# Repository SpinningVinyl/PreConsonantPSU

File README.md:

# PreConsonant PSU

### Basic Information

This is a 24V PSU I designed for use with the [PreConsonant phono preamplifier](https://github.com/SpinningVinyl/PreConsonant2021). It is basically a discrete feedback regulator with an error amplifier consisting of a single transistor (Q2 on the circuit diagram). It is designed to be used with a 24V transformer because I wanted to use an off-the-shelf 24V AC wall wart to power my phono preamplifier build. Since transformers typically have no-load output voltage that can be up to 20% higher than their rated voltage under full load, it was going to be too high for a standard 3-pin voltage regulator IC (e.g. LM7824).

### Technical specifications

 - Input voltage: between 21 and 30V AC (with the specified components)
 - Output voltage: approx. 24V DC
 - Load regulation: less than 1% at 100mA output current (component values have been calculated for output currents up to 500mA)
 - Ripple and noise: more than 60dB below the output level
 
### Documentation
The documentation (bill of materials and full circuit diagram) is located in the `docs` folder.

### Status of the project

The project has been built and tested.

### License
See the `LICENSE` file for details.

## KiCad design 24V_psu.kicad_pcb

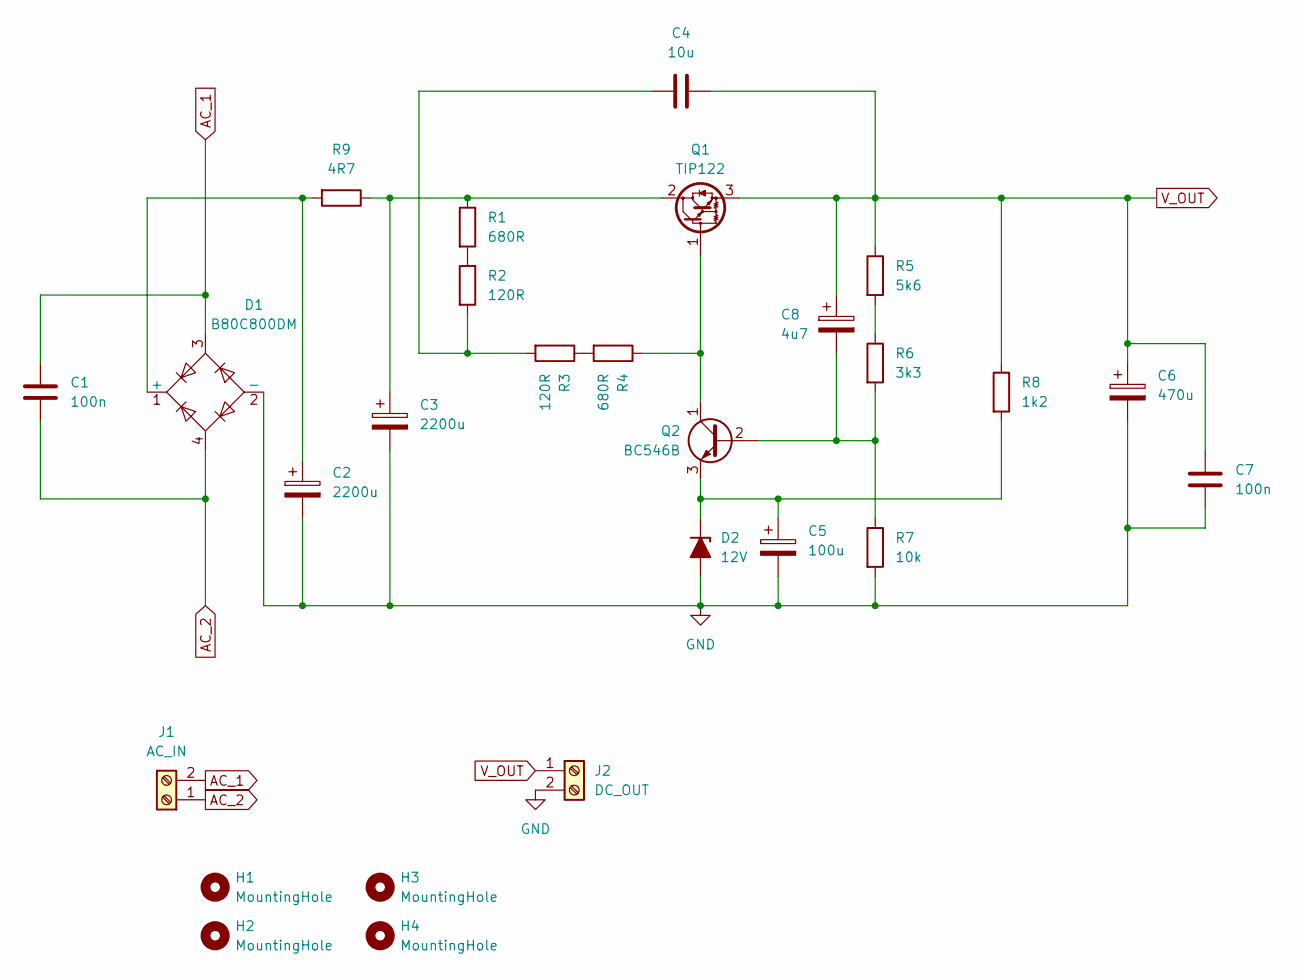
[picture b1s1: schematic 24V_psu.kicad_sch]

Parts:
C1, C7: 100n; C_Rect_L7.2mm_W3.5mm_P5.00mm_FKS2_FKP2_MKS2_MKP2
C2, C3: 2200u; CP_Radial_D18.0mm_P7.50mm
C4: 10u; C_Radial_D5.0mm_H11.0mm_P2.00mm
C5: 100u; CP_Radial_D10.0mm_P5.00mm
C6: 470u; CP_Radial_D12.5mm_P5.00mm
C8: 4u7; CP_Radial_D4.0mm_P2.00mm
D1: B80C800DM; Diode_Bridge_DIP-4_W7.62mm_P5.08mm
D2: 12V; D_DO-41_SOD81_P7.62mm_Horizontal
H1, H2, H3, H4: MountingHole; MountingHole_3.2mm_M3
J1: AC_IN; TerminalBlock_MaiXu_MX126-5.0-02P_1x02_P5.00mm
J2: DC_OUT; TerminalBlock_MaiXu_MX126-5.0-02P_1x02_P5.00mm
Q1: TIP122; TO-220-3_Vertical
Q2: BC546B; TO-92_HandSolder
R1, R4: 680R; R_Axial_DIN0207_L6.3mm_D2.5mm_P7.62mm_Horizontal
R2, R3: 120R; R_Axial_DIN0207_L6.3mm_D2.5mm_P7.62mm_Horizontal
R5: 5k6; R_Axial_DIN0207_L6.3mm_D2.5mm_P7.62mm_Horizontal
R6: 3k3; R_Axial_DIN0207_L6.3mm_D2.5mm_P7.62mm_Horizontal
R7: 10k; R_Axial_DIN0207_L6.3mm_D2.5mm_P7.62mm_Horizontal
R8: 1k2; R_Axial_DIN0207_L6.3mm_D2.5mm_P7.62mm_Horizontal
R9: 4R7; R_Axial_DIN0414_L11.9mm_D4.5mm_P5.08mm_Vertical

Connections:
AC_1: C1.1, D1.3, J1.2
AC_2: C1.2, D1.4, J1.1
GND: C2.2, C3.2, C5.2, C6.2, C7.2, D1.2 (-), D2.2 (A), J2.2, R7.2
unnamed: C4.2, R2.2, R3.2
unnamed: C2.1, D1.1 (+), R9.2
unnamed: C5.1, D2.1 (K), Q2.3 (E), R8.2
unnamed: Q1.1 (B), Q2.1 (C), R4.1
unnamed: C3.1, Q1.2 (C), R1.1, R9.1
unnamed: C8.2, Q2.2 (B), R6.2, R7.1
unnamed: R1.2, R2.1
unnamed: R3.1, R4.2
unnamed: R5.2, R6.1
V_OUT: C4.1, C6.1, C7.1, C8.1, J2.1, Q1.3 (E), R5.1, R8.1

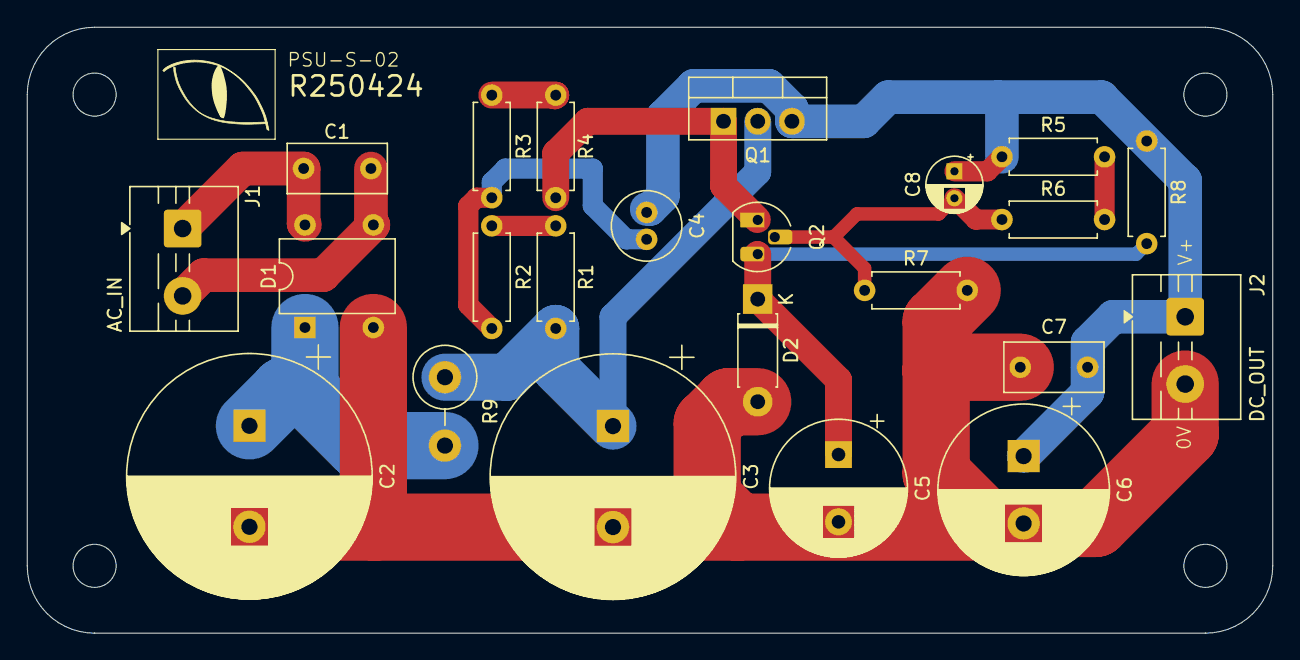
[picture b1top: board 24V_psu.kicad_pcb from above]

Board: 2 copper layers, 92.5 x 45.0 mm, 27 parts (0 on the bottom side), 13 nets.

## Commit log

2025-04-24 Initial public release
2025-04-24 Change C4 footprint to non-polarized
2025-04-24 Move R5, R6 and R8 to provide space for a heatsink
2025-04-24 Add C8 for slightly improved ripple rejection
2025-04-24 Change J1 and J2 to 5mm pitch
2025-04-24 Rotate R9 around
2025-04-24 add docs
2025-04-24 small updates
2025-04-24 specify that Q2 is an NPN transistor
